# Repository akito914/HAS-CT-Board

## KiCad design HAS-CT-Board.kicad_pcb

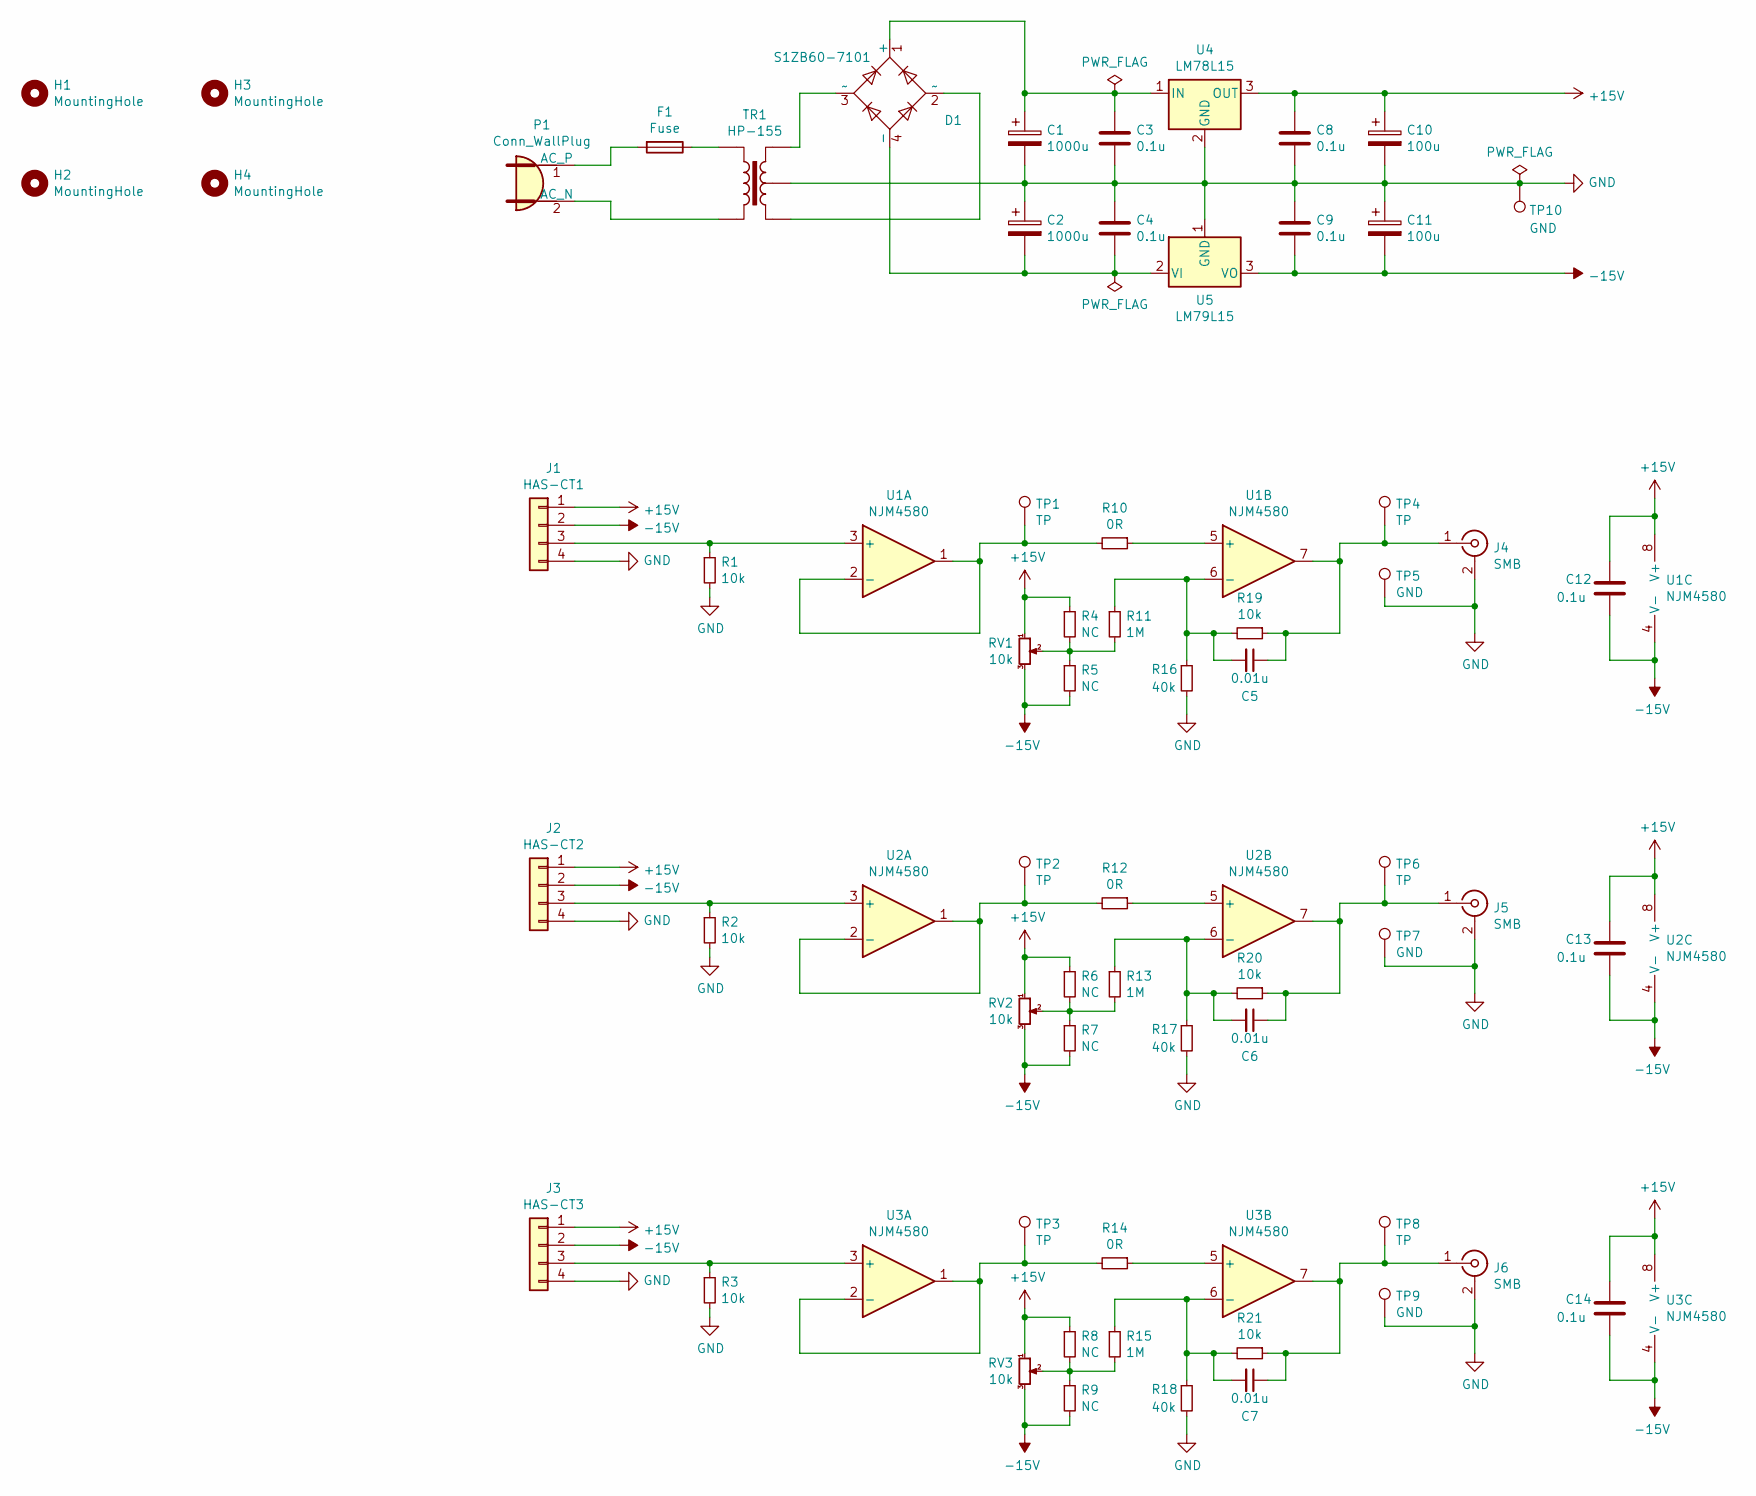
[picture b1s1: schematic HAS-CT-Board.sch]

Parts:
C1, C2: 1000u; CP_Radial_D10.0mm_P5.00mm
C3, C4, C8, C9, C12, C13, C14: 0.1u; C_0603_1608Metric
C5, C6, C7: 0.01u; C_0603_1608Metric
C10, C11: 100u; CP_Radial_D6.3mm_P2.50mm
D1: S1ZB60-7101; Diode_Bridge_DIP-4_W5.08mm_P2.54mm
F1: Fuse; FuseHolder_5.2mm
H1, H2, H3, H4: MountingHole; MountingHole_3.2mm_M3_noResist
J1: HAS-CT1; Molex_KK-254_AE-6410-04A_1x04_P2.54mm_Vertical
J2: HAS-CT2; Molex_KK-254_AE-6410-04A_1x04_P2.54mm_Vertical
J3: HAS-CT3; Molex_KK-254_AE-6410-04A_1x04_P2.54mm_Vertical
J4, J5, J6: SMB; SMB_Jack_Vertical
P1: Conn_WallPlug; AC-M04PB05
R1, R2, R3, R19, R20, R21: 10k; R_0603_1608Metric
R4, R5, R6, R7, R8, R9: NC; R_0603_1608Metric
R10, R12, R14: 0R; R_0603_1608Metric
R11, R13, R15: 1M; R_0603_1608Metric
R16, R17, R18: 40k; R_0603_1608Metric
RV1, RV2, RV3: 10k; Potentiometer_Bourns_3296W_Vertical
TP1, TP2, TP3, TP4, TP6, TP8: TP; TestPoint_Loop_D1.80mm_Drill1.0mm_Beaded
TP5, TP7, TP9, TP10: GND; TestPoint_Loop_D1.80mm_Drill1.0mm_Beaded
TR1: HP-155
U1, U2, U3: NJM4580; DIP-8_W7.62mm_Socket
U4: LM78L15; TO-92_Inline_Wide
U5: LM79L15; TO-92_Inline_Wide

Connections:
+15V: C8.1, C10.1, C12.1, C13.1, C14.1, J1.1, J2.1, J3.1, R4.1, R6.1, R8.1, RV1.1, RV2.1, RV3.1, U1.8 (V+), U2.8 (V+), U3.8 (V+), U4.3 (OUT)
-15V: C9.2, C11.2, C12.2, C13.2, C14.2, J1.2, J2.2, J3.2, R5.2, R7.2, R9.2, RV1.3, RV2.3, RV3.3, U1.4 (V-), U2.4 (V-), U3.4 (V-), U5.3 (VO)
GND: C1.2, C2.1, C3.2, C4.1, C8.2, C9.1, C10.2, C11.1, J1.4, J2.4, J3.4, J4.2 (Ext), J5.2 (Ext), J6.2 (Ext), R1.2, R2.2, R3.2, R16.2, R17.2, R18.2, TP5.1, TP7.1, TP9.1, TP10.1, TR1.2, U4.2 (GND), U5.1 (GND)
unnamed: C1.1, C3.1, D1.1 (+), U4.1 (IN)
unnamed: C2.2, C4.2, D1.4 (-), U5.2 (VI)
unnamed: C5.1, J4.1 (In), R19.1, TP4.1, U1.7
unnamed: C5.2, R11.1, R16.1, R19.2, U1.6 (-)
unnamed: C6.1, J5.1 (In), R20.1, TP6.1, U2.7
unnamed: C6.2, R13.1, R17.1, R20.2, U2.6 (-)
unnamed: C7.1, J6.1 (In), R21.1, TP8.1, U3.7
unnamed: C7.2, R15.1, R18.1, R21.2, U3.6 (-)
unnamed: D1.2 (~~), TR1.3
unnamed: D1.3 (~~), TR1.1
unnamed: F1.1, TR1.5
unnamed: F1.2, P1.1 (AC_P)
unnamed: J1.3, R1.1, U1.3 (+)
unnamed: J2.3, R2.1, U2.3 (+)
unnamed: J3.3, R3.1, U3.3 (+)
unnamed: P1.2 (AC_N), TR1.4
unnamed: R10.1, U1.5 (+)
unnamed: R10.2, TP1.1, U1.1, U1.2 (-)
unnamed: R4.2, R5.1, R11.2, RV1.2
unnamed: R12.1, U2.5 (+)
unnamed: R12.2, TP2.1, U2.1, U2.2 (-)
unnamed: R6.2, R7.1, R13.2, RV2.2
unnamed: R14.1, U3.5 (+)
unnamed: R14.2, TP3.1, U3.1, U3.2 (-)
unnamed: R8.2, R9.1, R15.2, RV3.2

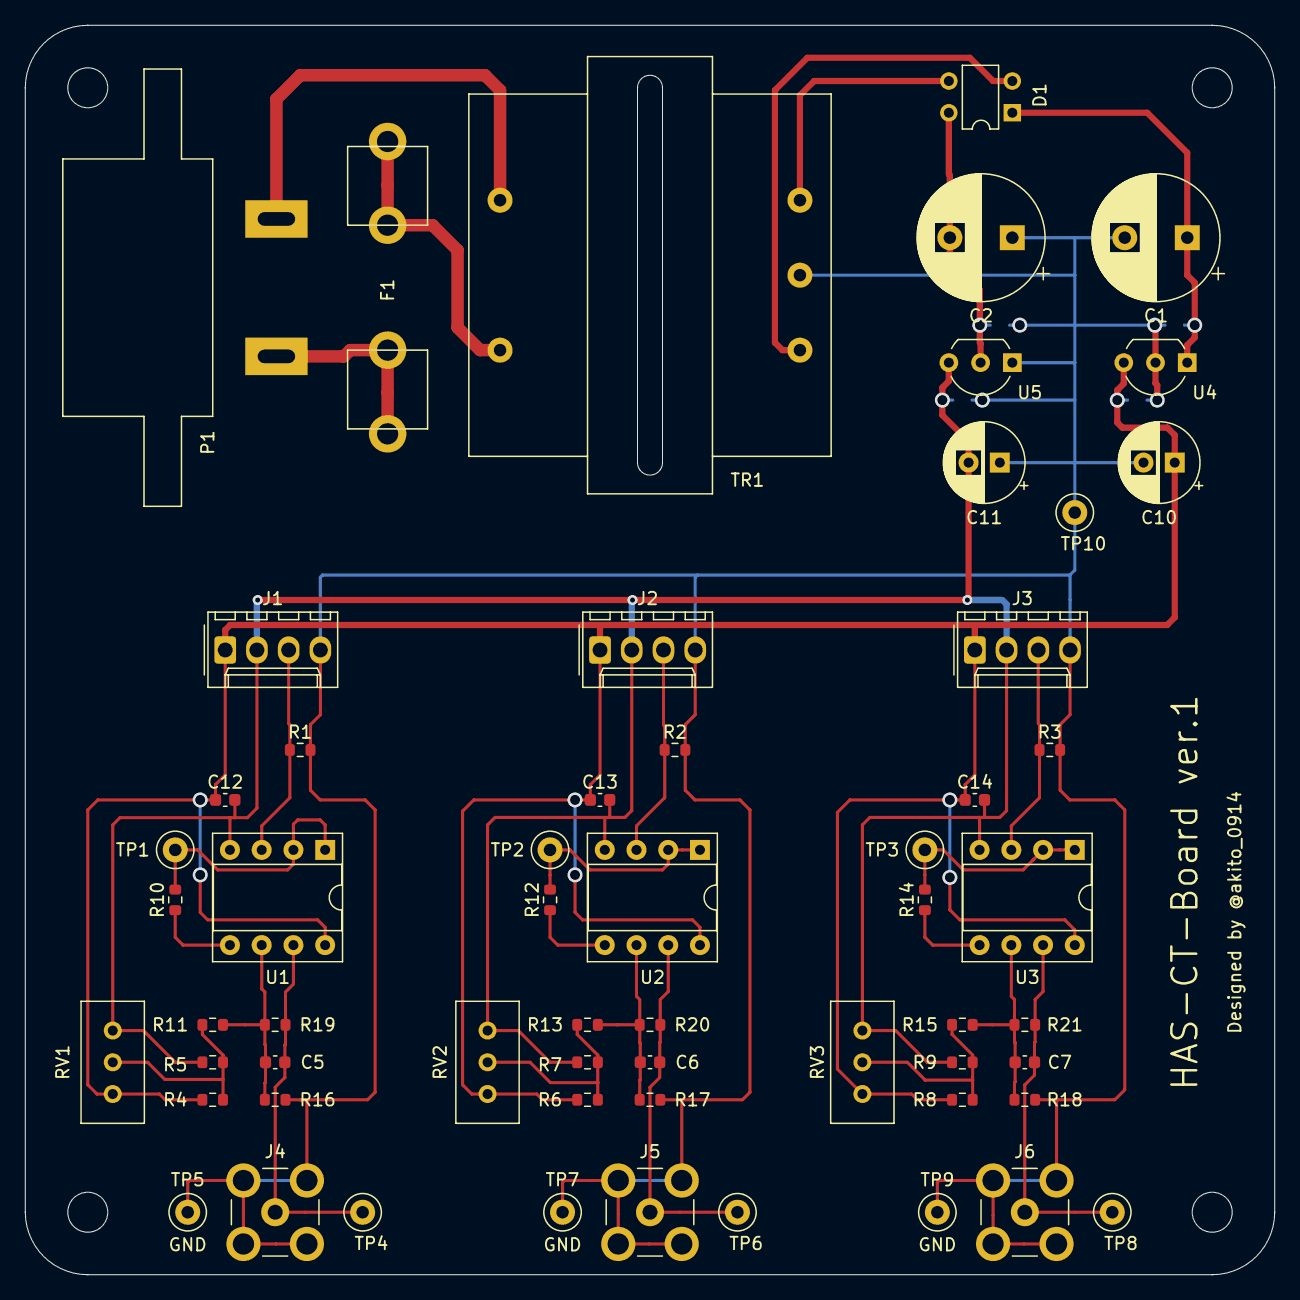
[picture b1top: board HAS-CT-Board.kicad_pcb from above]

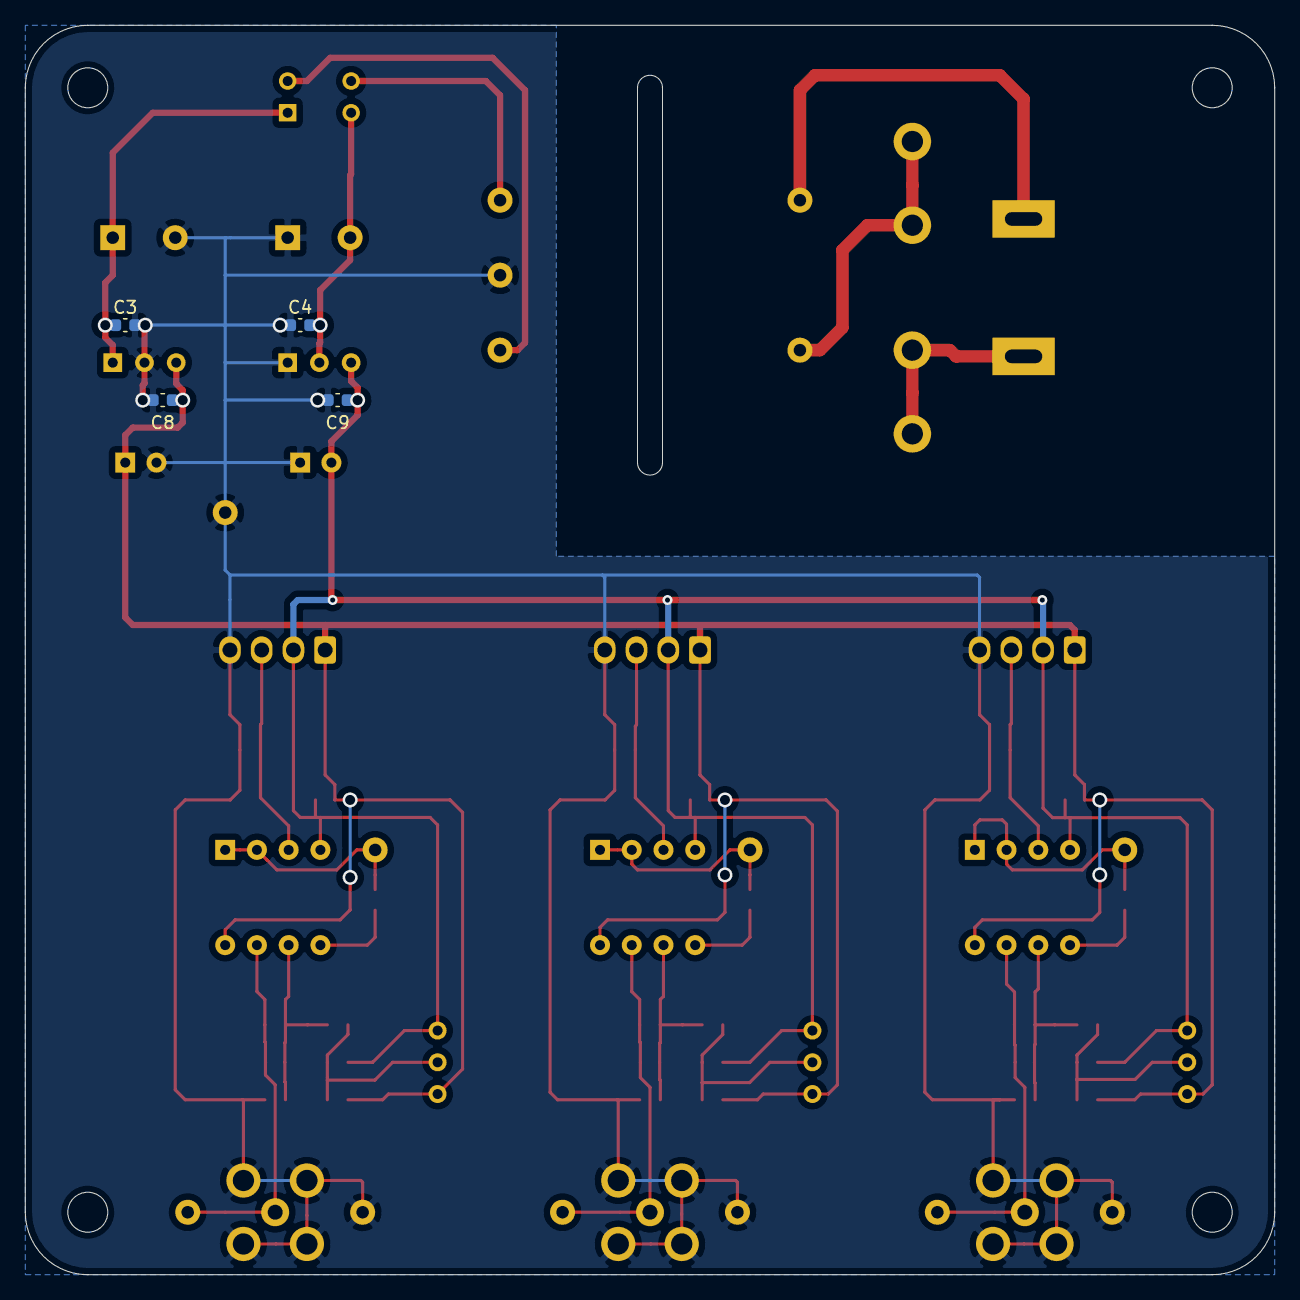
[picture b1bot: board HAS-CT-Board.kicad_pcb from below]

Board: 2 copper layers, 100.0 x 100.0 mm, 67 parts (4 on the bottom side), 28 nets.

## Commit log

2021-09-25 Add: 回路図
2021-09-25 Add: 配線のみ完了
2021-09-25 Update: PCB
2021-09-25 Update: 穴最大サイズを0.8mmに統一
2021-09-26 Add: ガーバー書き出し
